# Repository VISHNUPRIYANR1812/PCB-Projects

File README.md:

# PCB-Projects
Collection of my custom PCB designs, including schematics, Gerber files, and project details.

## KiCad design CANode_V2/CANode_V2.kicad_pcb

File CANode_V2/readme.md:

#  SPI-CAN Node V1 to CANode V2: A SMARTER, WIRELESS UPGRADE! 

The V2 design introduces critical improvements to support wireless diagnostics, cloud integration, and real-time monitoring, making it a game-changer for CAN-based applications in automotive, industrial automation, and IoT systems.

## 🔍 V1 Limitations:

- MCP2515 CAN Controller with TJA1050 Transceiver provided standard SPI-CAN conversion but lacked debugging capabilities.
- Requires host MCU for programming and Application circuit

  🔗 View SPI-CAN Node V1 here: https://github.com/VISHNUPRIYANR1812/PCB-Projects/tree/main/Isolated-SPI-CAN-Node

## ⚙️ V2 Enhancements & Architecture:

https://github.com/user-attachments/assets/42ad2c8d-1fca-4bb1-90af-36ff37ddd96d

### ✅ MCU Upgrade:
- ESP8266 with Wi-Fi connectivity for remote CAN node management, cloud logging, and OTA updates.

### ✅ Level Shifting:
- TXB0108PWR Bi-Directional Logic Converter for seamless 3.3V↔5V communication between ESP8266 and MCP2515.

### ✅ CAN Controller & Transceiver:
- MCP2515 SPI-CAN Controller paired with TJA1050 CAN Transceiver for robust CAN communication.

### ✅ USB-UART Debugging:
- CH340G UART Controller with RTS/DTR auto-reset for hassle-free firmware updates and debugging.

### ✅ Power Management:
- LD1117S12TR LDO Regulator ensuring a stable 3.3V supply for ESP8266 and MCP2515.

### ✅ Termination & Protection:
- JST_XH 5V Power Connector for secure power input.
- 120Ω selectable CAN termination for network flexibility.
- ESD protection components for enhanced durability.

### ✅ Display & Expansion:
- OLED Display Header for real-time CAN message visualization.

## 💡 Key Advancements:
- 🚀 **IoT-enabled CAN Network** – Cloud integration, remote diagnostics, and OTA firmware updates.
- 🚀 **Wi-Fi-based Configuration** – Web dashboard for real-time monitoring & control.
- 🚀 **Advanced Debugging & Expansion** – Improved power stability, logic isolation, and interface flexibility.

This V2 iteration brings higher integration, improved debugging, and wireless intelligence, redefining modern embedded networking for automotive, industrial, and IoT applications.

## 📌 Hashtags:
#CANBus #IoT #EmbeddedSystems #ESP8266 #MCP2515 #PCBDesign #WirelessCommunication #EdgeComputing #IndustrialAutomation #CloudIntegration #Automation #SmartDevices #IoTDevelopment #SmartManufacturing #OpenSourceHardware #HardwareDesign #CircuitDesign #IoTNetworking #IoTSolutions #ProductDevelopment #TechInnovation

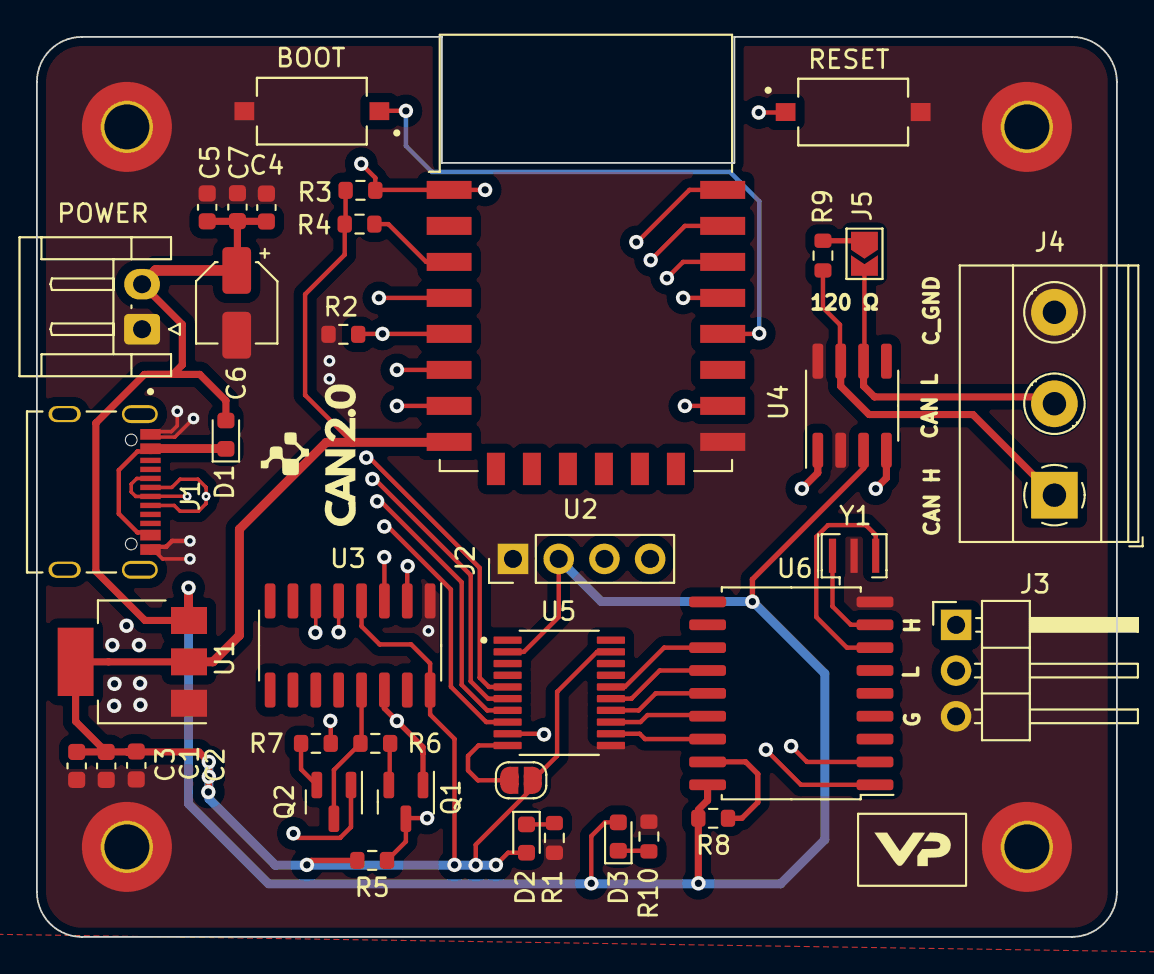
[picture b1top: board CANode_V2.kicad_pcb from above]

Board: 4 copper layers, 60.0 x 50.0 mm, 42 parts (0 on the bottom side), 38 nets.

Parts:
BOOT: BOOT0; SW_TS09-63-25-WT-260-SMT-TR
C1: 22uF; C_0603_1608Metric
C2: 10uF; C_0603_1608Metric
C3, C5, C7: 0.1uF; C_0603_1608Metric
C4: 100nF; C_0603_1608Metric
C6: 10uFE/16V; CP_Elec_4x3
D1: SS34; D_0603_1608Metric
D2, D3: LED; LED_0603_1608Metric
H1, H2, H3, H4: MountingHole_Pad; MountingHole_2.5mm_Pad_TopBottom
J1: USB_C; VALCON_CSP-USC16-TR
J2: I2C; PinHeader_1x04_P2.54mm_Vertical
J3: JUMP_CAN; PinHeader_1x03_P2.54mm_Horizontal
J4: SCR_CAN; TerminalBlock_Phoenix_MKDS-1,5-3-5.08_1x03_P5.08mm_Horizont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
J5: 120R_T; SolderJumper-2_P1.3mm_Open_TrianglePad1.0x1.5mm
JP1: OE; SolderJumper-2_P1.3mm_Open_RoundedPad1.0x1.5mm
POWER: PW_IN; JST_EH_S2B-EH_1x02_P2.50mm_Horizontal
Q1, Q2: S8050; SOT-23
R1, R2, R3, R4, R5, R6, R7, R8, R10: 10K; R_0603_1608Metric
R9: 120R; R_0603_1608Metric
RESET: NRST; SW_TS09-63-25-WT-260-SMT-TR
U1: LD1117S12TR_SOT223; SOT-223-3_TabPin2
U2: ESP-12F; ESP-12E
U3: CH340C; SOIC-16_3.9x9.9mm_P1.27mm
U4: TJA1050; SOIC-8_3.9x4.9mm_P1.27mm
U5: TXB0108PWR; SOP65P640X120-20N
U6: MCP2515-xSO; SOIC-18W_7.5x11.6mm_P1.27mm
Y1: 8MHz/22pF; Resonator_SMD_Murata_CSTxExxV-3Pin_3.0x1.1mm

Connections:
+3V3: C1.2, C2.2, C3.2, D2.2 (A), JP1.2 (B), R3.2, R4.2, R5.2, U1.2 (VO), U2.8 (VCC), U3.4 (V3), U3.16 (VCC), U5.19 (VCCB)
CAN_H: J3.1, J4.1, R9.1, U4.7 (CAN_H)
CAN_L: J3.2, J4.2, J5.2, U4.6 (CAN_L)
CRX: U4.4 (RXD), U6.2 (RXCAN)
CS: U5.12 (B8), U6.16 (~CS)
CTX: U4.1 (TXD), U6.1 (TXCAN)
D+: J1.A6 (D+), J1.B6 (D+), U3.5 (UD+)
D-: J1.A7 (D-), J1.B7 (D-), U3.6 (UD-)
DTR: Q1.1 (E), R7.1, U3.14 (~RTS)
EN: R4.1, U2.3 (EN)
GND: BOOT.2, C1.1, C2.1, C3.1, C4.1, C5.2, C6.2, C7.2, H1.1, H2.1, H3.1, H4.1, J1.A1 (GND), J1.A12 (GND), J1.B1 (GND), J1.B12 (GND), J2.1, J3.3, J4.3, POWER.1, R1.1, R2.1, R10.1, RESET.2, U1.1 (GND), U2.15 (GND), U3.1 (GND), U4.2 (GND), U4.8 (S), U5.11 (GND), U6.9 (VSS), Y1.2
GPIO0: BOOT.1, Q1.3 (C), R5.1, U2.18 (GPIO0)
GPIO1: U2.22 (GPIO1/TXD), U3.3 (RXD)
GPIO3: U2.21 (GPIO3/RXD), U3.2 (TXD)
GPIO4: J2.4, U2.19 (GPIO4)
GPIO5: J2.3, U2.20 (GPIO5)
GPIO12: U2.6 (GPIO12), U5.8 (A7)
GPIO13: U2.7 (GPIO13), U5.7 (A6)
GPIO14: R2.2, U2.5 (GPIO14), U5.6 (A5)
GPIO15: U2.16 (GPIO15), U5.9 (A8)
GPIO16: U2.4 (GPIO16), U5.5 (A4)
INT: U5.16 (B4), U6.12 (~INT)
MISO: U5.13 (B7), U6.15 (SO)
MOSI: U5.14 (B6), U6.14 (SI)
unnamed: D2.1 (K), R1.2
unnamed: D3.1 (K), R10.2
unnamed: D1.1 (K), J1.A4 (VBUS), J1.A9 (VBUS), J1.B4 (VBUS), J1.B9 (VBUS)
unnamed: J5.1, R9.2
unnamed: JP1.1 (A), U5.10 (OE)
unnamed: Q1.2 (B), R6.2
unnamed: Q2.2 (B), R7.2
unnamed: R8.2, U6.17 (~RESET)
unnamed: U6.7 (OSC2), Y1.3
unnamed: U6.8 (OSC1), Y1.1
RST: Q2.1 (E), R3.1, RESET.1, U2.1 (~RST)
RTS: Q2.3 (C), R6.1, U3.13 (~DTR)
SCK: U5.15 (B5), U6.13 (SCK)
VBUS: C4.2, C5.1, C6.1, C7.1, D1.2 (A), D3.2 (A), J2.2, POWER.2, R8.1, U1.3 (VI), U4.3 (VCC), U5.2 (VCCA), U6.18 (VDD)

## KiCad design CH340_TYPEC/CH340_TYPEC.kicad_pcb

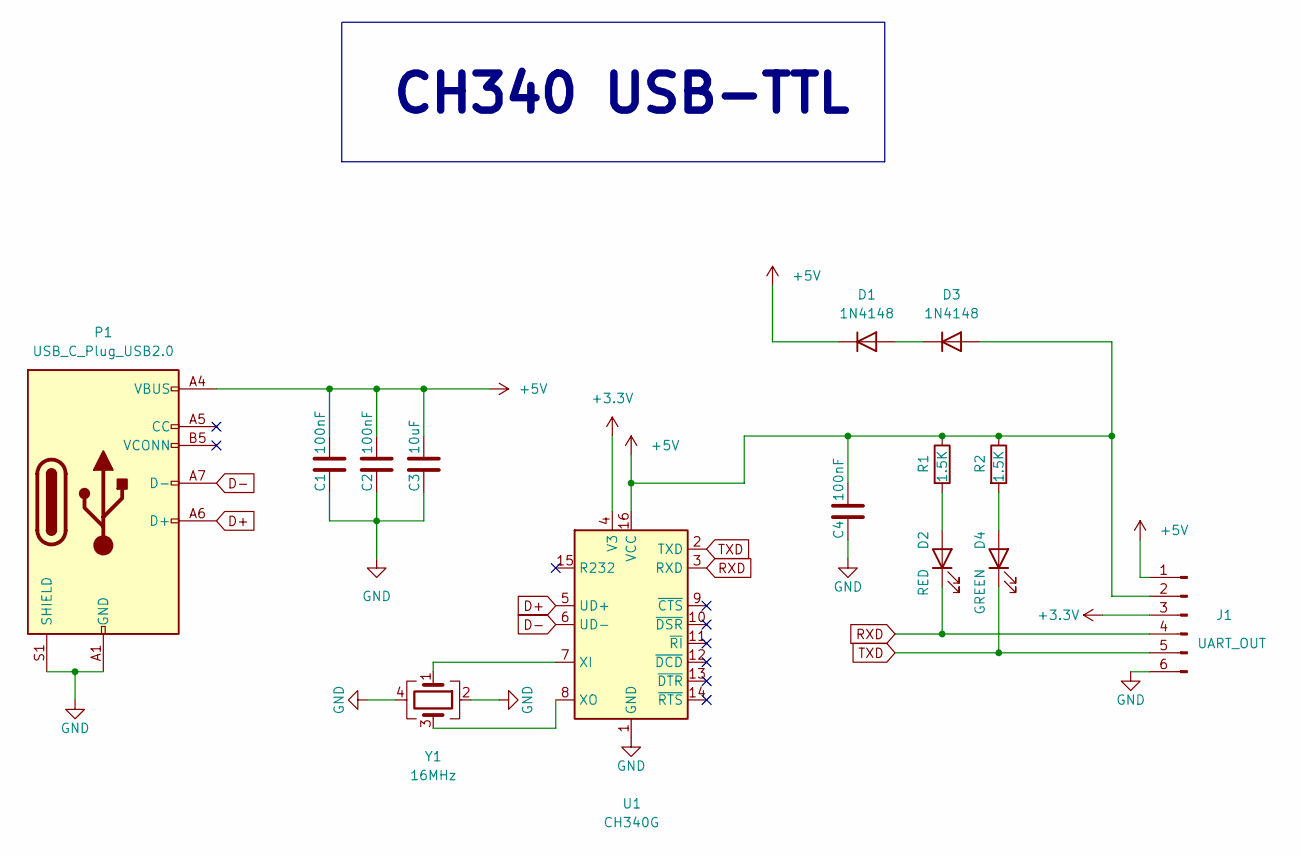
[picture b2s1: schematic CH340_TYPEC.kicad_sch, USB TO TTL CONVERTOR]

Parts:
C1, C2, C4: 100nF; C_0603_1608Metric
C3: 10uF; C_0603_1608Metric
D1, D3: 1N4148; D_SOD-123F
D2: RED; LED_0603_1608Metric
D4: GREEN; LED_0603_1608Metric
J1: UART_OUT; PinHeader_1x06_P2.54mm_Horizontal
P1: USB_C_Plug_USB2.0; USB_C_Receptacle_HRO_TYPE-C-31-M-12
R1, R2: 1.5K; R_0603_1608Metric
U1: CH340G; SOIC-16_3.9x9.9mm_P1.27mm
Y1: 16MHz; Crystal_SMD_3225-4Pin_3.2x2.5mm

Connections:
+3V3: J1.3, U1.4 (V3)
+5V: C1.1, C2.1, C3.1, C4.1, D1.1 (K), D3.2 (A), J1.1, J1.2, P1.A4 (VBUS), P1.A9 (VBUS), P1.B4 (VBUS), P1.B9 (VBUS), R1.1, R2.1, U1.16 (VCC)
D+: P1.A6 (D+), U1.5 (UD+)
D-: P1.A7 (D-), U1.6 (UD-)
GND: C1.2, C2.2, C3.2, C4.2, J1.6, P1.A1 (GND), P1.A12 (GND), P1.B1 (GND), P1.B12 (GND), P1.S1 (SHIELD), U1.1 (GND), Y1.2, Y1.4
unnamed: D1.2 (A), D3.1 (K)
unnamed: D2.2 (A), R1.2
unnamed: D4.2 (A), R2.2
unnamed: U1.7 (XI), Y1.1
unnamed: U1.8 (XO), Y1.3
RXD: D2.1 (K), J1.4, U1.3 (RXD)
TXD: D4.1 (K), J1.5, U1.2 (TXD)

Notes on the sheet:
CH340 USB-TTL

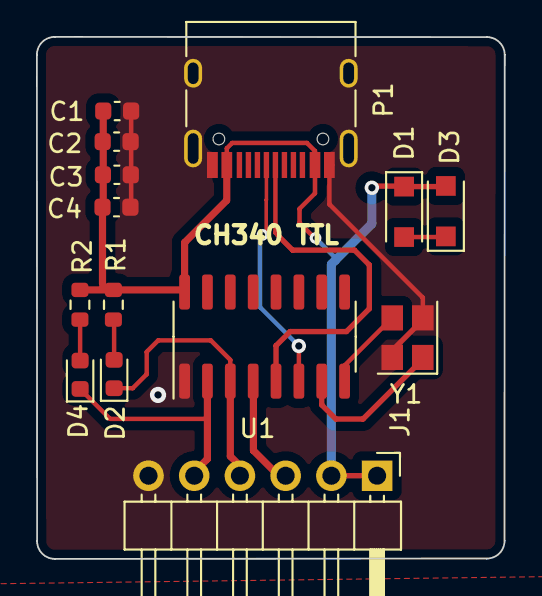
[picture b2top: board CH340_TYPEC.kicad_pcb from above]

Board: 2 copper layers, 26.0 x 29.0 mm, 14 parts (0 on the bottom side), 12 nets.

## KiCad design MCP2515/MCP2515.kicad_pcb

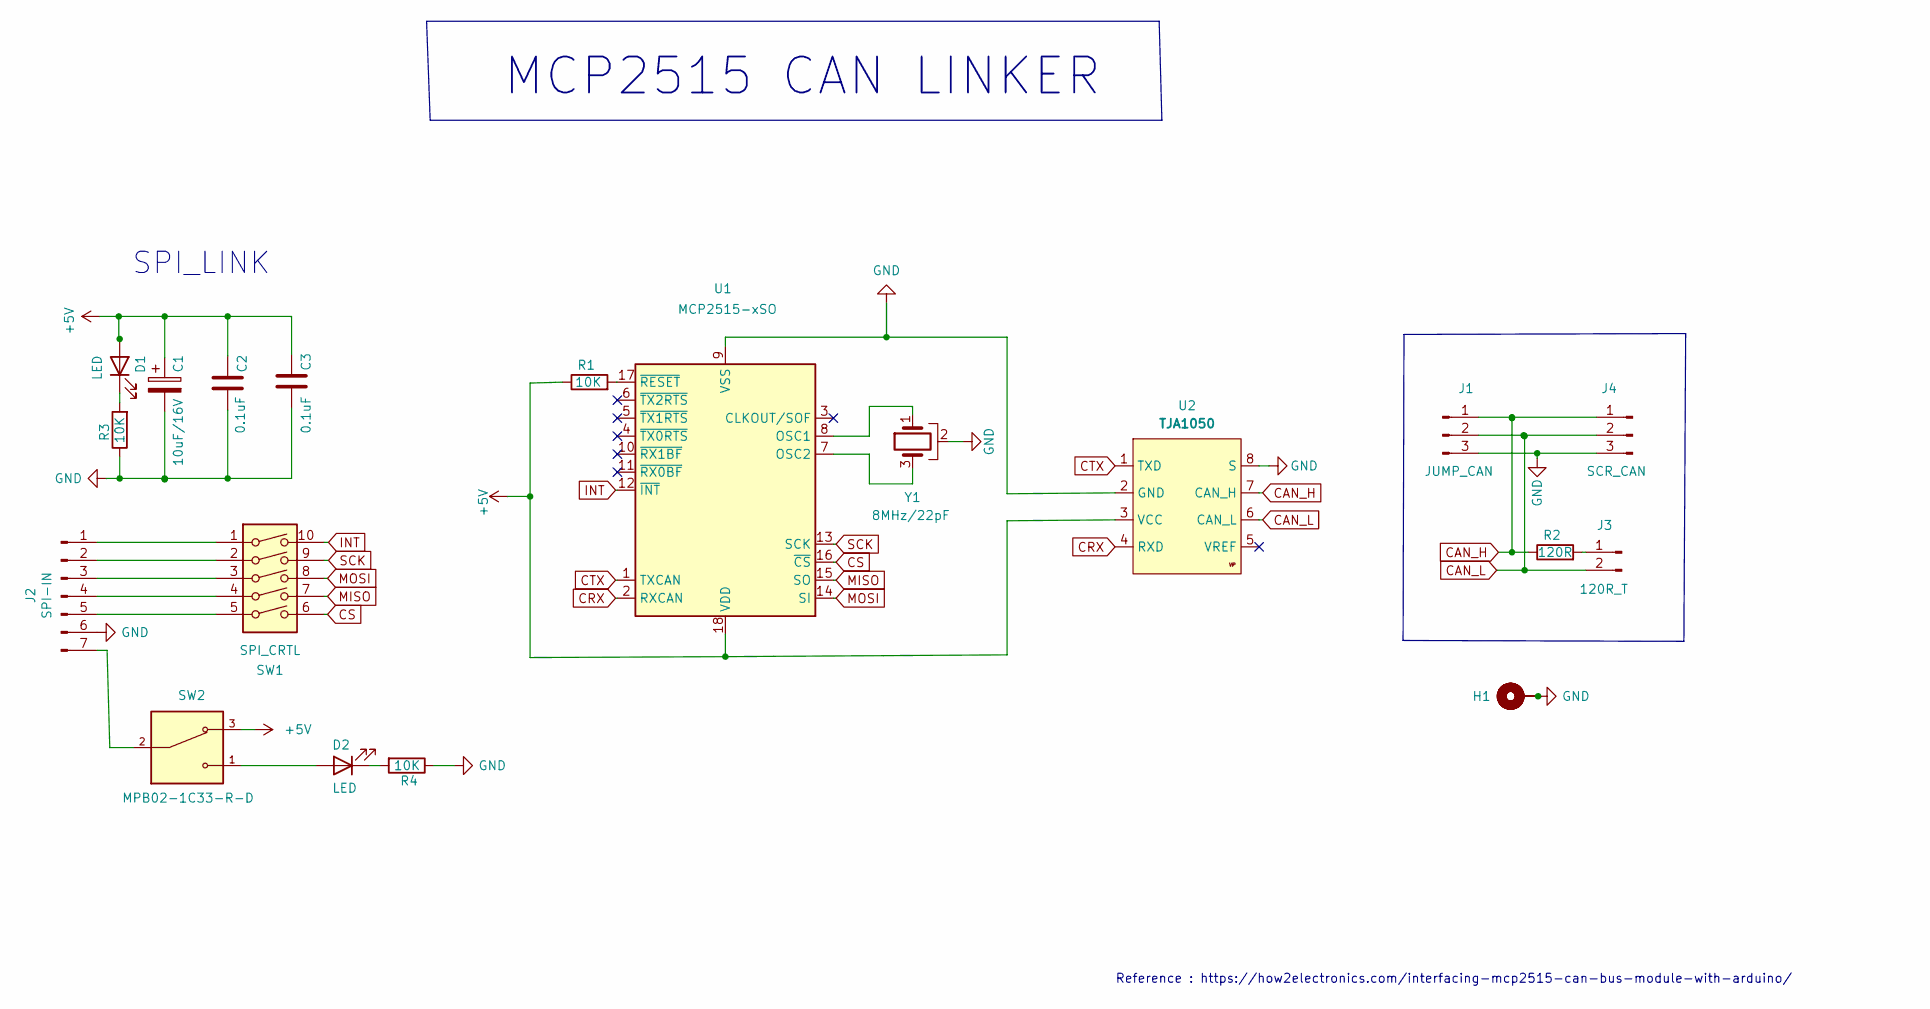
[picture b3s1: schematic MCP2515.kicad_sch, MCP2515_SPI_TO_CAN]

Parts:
C1: 10uF/16V; CP_Elec_4x3
C2, C3: 0.1uF; C_0805_2012Metric
D1, D2: LED; LED_0805_2012Metric
H1, H2, H3, H4: MountingHole_Pad; MountingHole_2.5mm_Pad_TopBottom
J1: JUMP_CAN; PinHeader_1x03_P2.54mm_Horizontal
J2: SPI-IN; PinHeader_1x07_P2.54mm_Vertical
J3: 120R_T; SolderJumper-2_P1.3mm_Open_TrianglePad1.0x1.5mm
J4: SCR_CAN; TerminalBlock_Phoenix_MKDS-1,5-3-5.08_1x03_P5.08mm_Horizont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
R1, R3, R4: 10K; R_0805_2012Metric
R2: 120R; R_0805_2012Metric
SW1: SPI_CRTL; SW_DIP_SPSTx05_Slide_KingTek_DSHP05TS_W7.62mm_P1.27mm
SW2: MPB02-1C33-R-D; SW_MPB02-1C33-R-D; PARTREV 1.0
U1: MCP2515-xSO; SOIC-18W_7.5x11.6mm_P1.27mm; LCSC C153782
U2: TJA1050; SOIC-8_3.9x4.9mm_P1.27mm; LCSC C6952
Y1: 8MHz/22pF; Resonator_SMD_Murata_CSTxExxV-3Pin_3.0x1.1mm

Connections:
+5V: C1.1, C2.1, C3.1, D1.2 (A), R1.1, SW2.3, U1.18 (VDD), U2.3 (VCC)
CAN_H: J1.1, J4.1, R2.1, U2.7 (CAN_H)
CAN_L: J1.2, J3.2, J4.2, U2.6 (CAN_L)
CRX: U1.2 (RXCAN), U2.4 (RXD)
CS: SW1.6, U1.16 (~CS)
CTX: U1.1 (TXCAN), U2.1 (TXD)
INT: SW1.10, U1.12 (~INT)
MISO: SW1.7, U1.15 (SO)
MOSI: SW1.8, U1.14 (SI)
unnamed: D1.1 (K), R3.2
unnamed: D2.1 (K), R4.2
unnamed: D2.2 (A), SW2.1
unnamed: J2.1, SW1.1
unnamed: J2.2, SW1.2
unnamed: J2.3, SW1.3
unnamed: J2.4, SW1.4
unnamed: J2.5, SW1.5
unnamed: J2.7, SW2.2
unnamed: J3.1, R2.2
unnamed: R1.2, U1.17 (~RESET)
unnamed: U1.7 (OSC2), Y1.3
unnamed: U1.8 (OSC1), Y1.1
SCK: SW1.9, U1.13 (SCK)

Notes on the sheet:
Reference : https://how2electronics.com/interfacing-mcp2515-can-bus-module-with-arduino/
MCP2515 CAN LINKER
SPI_LINK

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
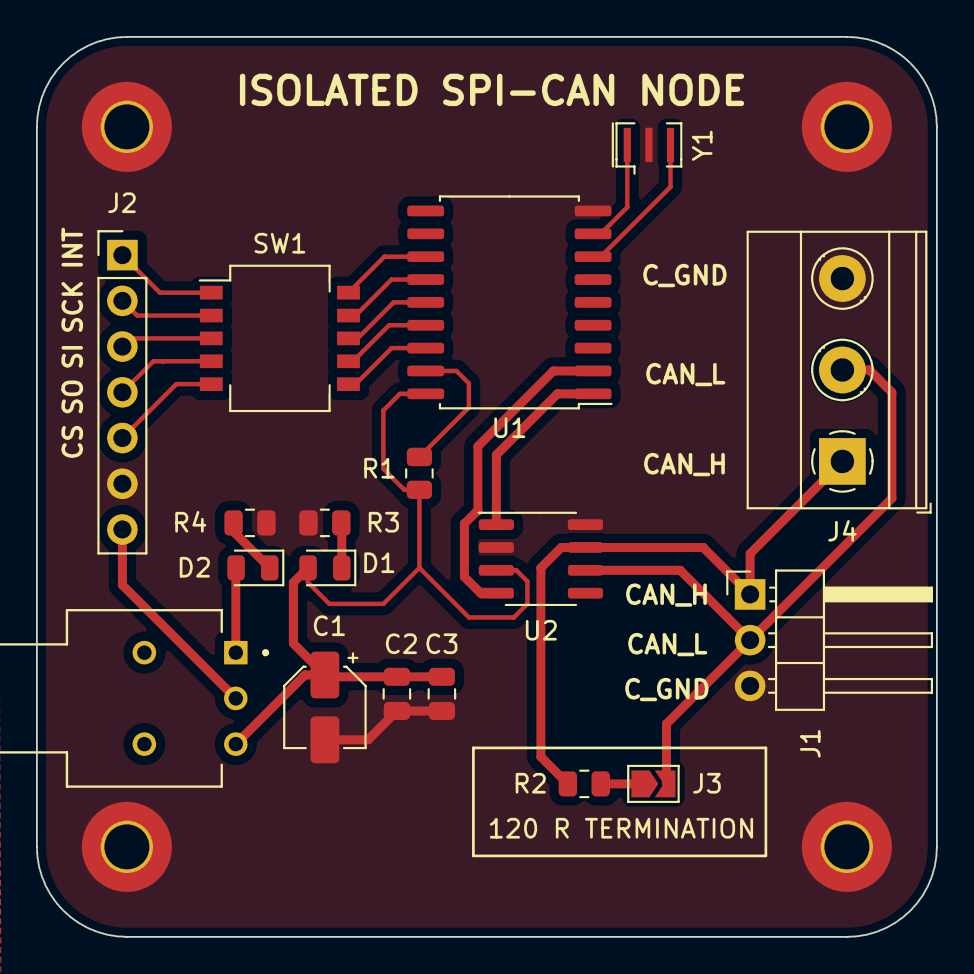
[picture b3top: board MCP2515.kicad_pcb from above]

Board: 2 copper layers, 50.0 x 50.0 mm, 22 parts (0 on the bottom side), 24 nets.

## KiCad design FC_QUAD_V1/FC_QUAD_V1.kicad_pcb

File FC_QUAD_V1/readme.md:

Here my latest custom-designed flight controller PCB, developed for Cost effective & Minimalistic solid performance drone applications. This design integrates essential features for real-time flight control, precise navigation, and efficient data handling, making it a robust solution for UAV systems.

## 🔹 System Specifications:

- **MCU:** STM32F411CEU6 – ARM Cortex-M4 FPU for real-time processing.
- **10 DOF IMU for precise motion sensing:**
  - **TDK MPU6050** – 6-axis gyroscope & accelerometer for stabilization.
  - **Honeywell HMC5883L** – 3-axis mag for accurate heading estimation.
  - **Bosch BMP180** – H-precision barometric sensor for altitude data.
- **SBUS input** for receiver communication.
- **UART interface** for GPS module integration.
- **SPI Testpoint** for Blackbox logging & mission data storage.
- **I2C support** up to 800KHz with an external I2C port for sensor expansion.
- **USB-C interface** for firmware updates, tuning, and debugging.
- **RGB Neo-pixel LED** support for status indication.
- **JST_XH connector** for power module with V_SENSE & I_SENSE for real-time voltage & current monitoring.

## 🔹 PCB Specifications:

- **4-layer PCB stack-up** optimized for signal integrity & thermal performance:
  - **Layer 1:** Mixed plane (high-speed signals & power distribution).
  - **Layer 2:** Signal plane (optimized routing for minimal EMI).
  - **Layer 3:** Dedicated ground plane (low-noise operation).
  - **Layer 4:** Power plane (stable power distribution).
- **Thermal relief vias** to enhance heat dissipation.
- **Copper-filled unused regions** for improved EMC and signal integrity.
- **Well-organized ports and pin configurations** for seamless connectivity.

This project was designed with a focus on cost-efficiency, modularity, and real-time performance to meet the demands of modern UAV systems. Looking forward to further testing and optimizations.

Would love to hear your thoughts and feedback!

### Hashtags:

#PCBDesign #EmbeddedSystems #UAVTechnology #ElectronicsEngineering #AutonomousSystems #FutureOfDrones  
#DroneIndia #TechTrends #AviationMastery #DroneCareers

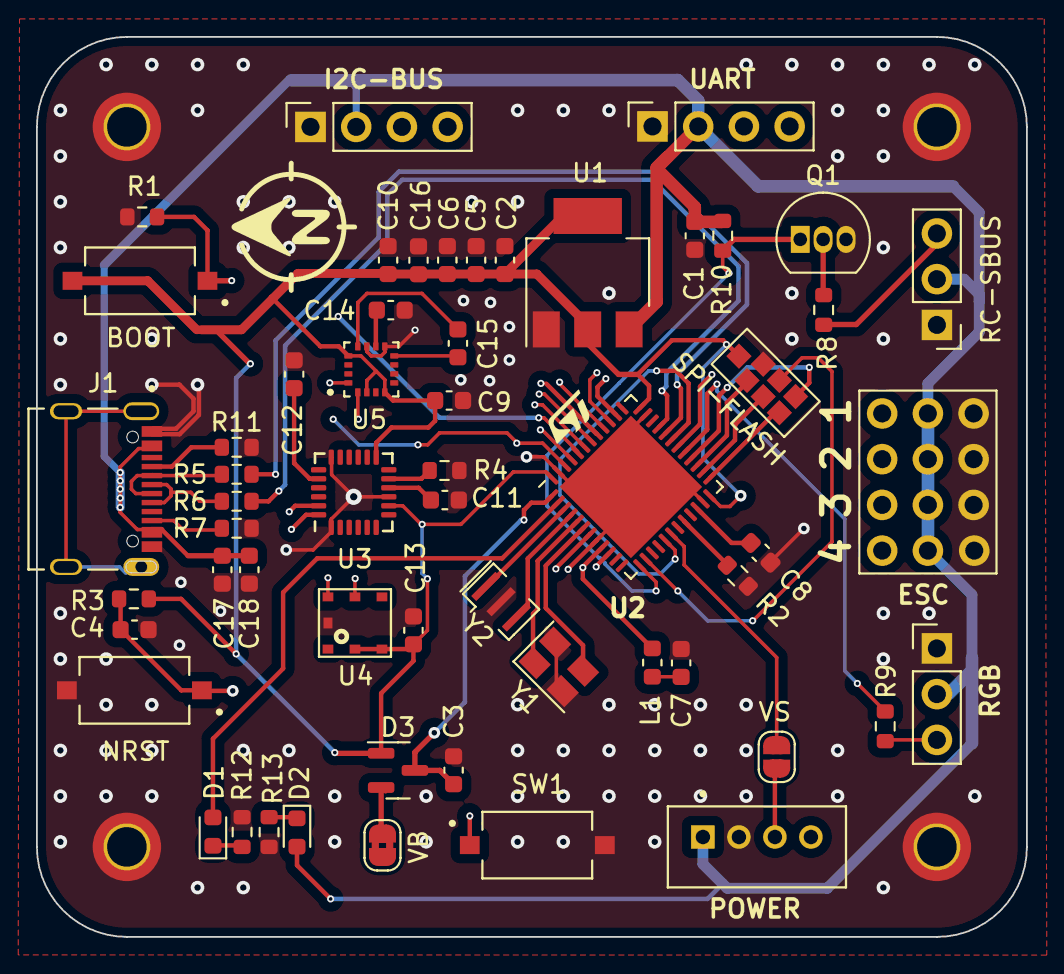
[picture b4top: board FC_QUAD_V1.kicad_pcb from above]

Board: 4 copper layers, 55.0 x 50.0 mm, 60 parts (0 on the bottom side), 53 nets.

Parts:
BOOT: BOOT0; SW_TS09-63-25-WT-260-SMT-TR
C1, C2, C4, C5, C6, C7, C17, C18: 100nF; C_0603_1608Metric
C3: 100uF; C_0603_1608Metric
C8: 2.2uF; C_0603_1608Metric
C9: 0.01uF; C_0603_1608Metric
C10, C11, C13, C16: 0.1uF; C_0603_1608Metric
C12: 2.2nF; C_0603_1608Metric
C14: 4.7uF; C_0603_1608Metric
C15: 0.22uF; C_0603_1608Metric
D1, D2: LED; LED_0603_1608Metric
D3: BAT54C; SOT-23
ESC: 4PIN_ESC; Esc_connector_4M
H1, H2, H3, H4: MountingHole_Pad; MountingHole_2.2mm_M2_DIN965_Pad_TopBottom
I2C-BUS: I2C; PinSocket_1x04_P2.54mm_Vertical
J1: CSP-USC16-TR; VALCON_CSP-USC16-TR
L1: 10uH; L_0603_1608Metric
NRST: NRST; SW_TS09-63-25-WT-260-SMT-TR
POWER: POWER MODULE; JST_B4B-PH-K
Q1: BC547; TO-92_Inline
R1, R2, R10, R12, R13: 10K; R_0603_1608Metric
R3: NC; R_0603_1608Metric
R4: 1K; R_0603_1608Metric
R5, R6: 10R; R_0603_1608Metric
R7, R11: 5.8K; R_0603_1608Metric
R8: 4.7K; R_0603_1608Metric
R9: 470R; R_0603_1608Metric
RC-SBUS: SBUS; PinHeader_1x03_P2.54mm_Vertical
RGB: RGB; PinHeader_1x03_P2.54mm_Vertical
SPI-FLASH: SPI-BLACKBOX; 7_TP
SW1: KEY; SW_TS09-63-25-WT-260-SMT-TR
U1: LD1117S12TR_SOT223; SOT-223-3_TabPin2
U2: STM32F411CEUx; QFN-48-1EP_7x7mm_P0.5mm_EP5.6x5.6mm
U3: MPU-6050; InvenSense_QFN-24_4x4mm_P0.5mm
U4: BMP180
U5: HMC5883L-TR
UART: UART; PinSocket_1x04_P2.54mm_Vertical
VB: VBAT; SolderJumper-2_P1.3mm_Bridged2Bar_RoundedPad1.0x1.5mm
VS: V_SENSE; SolderJumper-2_P1.3mm_Open_RoundedPad1.0x1.5mm
Y1: 25MHz/12pF; Crystal_SMD_SeikoEpson_TSX3225-4Pin_3.2x2.5mm
Y2: 32.7KHz/6pF; Resonator_SMD_Murata_CSTxExxV-3Pin_3.0x1.1mm

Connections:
+3V3: BOOT.2, C2.2, C5.2, C6.2, C9.2, C10.2, C13.2, C16.1, D3.1, R3.1, SPI-FLASH.7, U1.2 (VO), U2.24 (VDD), U2.36 (VDD), U2.48 (VDD), U3.8 (VDDIO), U3.13 (VDD), U4.2 (VDD), U4.3 (VDDIO), U5.2 (VDD), U5.4 (S1), U5.13 (VDDIO)
BOOT0: BOOT.1, R1.2, U2.44 (BOOT0)
CS: SPI-FLASH.5, U2.14 (PA4)
DN: J1.A7 (DN1), J1.B7 (DN2), R5.1
DP: J1.A6 (DP1), J1.B6 (DP2), R6.1
GND: C1.1, C2.1, C3.2, C4.2, C5.1, C6.1, C7.1, C8.1, C9.1, C10.1, C11.1, C12.2, C13.1, C14.1, C16.2, C17.1, C18.1, ESC.1 (GND), ESC.2 (GND), ESC.3 (GND), ESC.4 (GND), H1.1, H2.1, H3.1, H4.1, I2C-BUS.1, J1.A1 (GND_A), J1.A12 (GND_A), J1.B1 (GND_B), J1.B12 (GND_B), NRST.2, POWER.2, Q1.3 (E), R1.1, R2.1, R4.1, R7.2, R11.1, R12.2, R13.2, RC-SBUS.1, RGB.1, SPI-FLASH.6, SW1.2, U1.1 (GND), U2.8 (VSSA), U2.23 (VSS), U2.35 (VSS), U2.47 (VSS), U2.49 (VSS), U3.1 (CLKIN), U3.9 (AD0), U3.18 (GND), U4.7 (GND), U5.9 (GND), U5.11 (GND), UART.1, Y1.2, Y1.4, Y2.2
MISO: SPI-FLASH.3, U2.27 (PB14)
MOSI: SPI-FLASH.4, U2.28 (PB15)
MOT1: ESC.9 (M1), U2.40 (PB4)
MOT2: ESC.10 (M2), U2.41 (PB5)
MOT3: ESC.11 (M3), U2.42 (PB6)
MOT4: ESC.12 (M4), U2.43 (PB7)
NRST: C4.1, NRST.1, R3.2, U2.7 (NRST)
NSS: SPI-FLASH.1, U2.25 (PB12)
unnamed: C8.2, U2.22 (VCAP1)
unnamed: C11.2, U3.10 (REGOUT)
unnamed: C12.1, U3.20 (CPOUT)
unnamed: C14.2, U5.10 (C1)
unnamed: C15.1, U5.12 (SETC)
unnamed: C15.2, U5.8 (SETP)
unnamed: D1.1 (K), R12.1
unnamed: D2.1 (K), R13.1
unnamed: D3.2, VB.1 (A)
unnamed: J1.A5 (CC1), R11.2
unnamed: J1.B5 (CC2), R7.1
unnamed: R9.1, RGB.3
unnamed: R8.2, RC-SBUS.3
unnamed: L1.1, U2.9 (VDDA)
unnamed: Q1.2 (B), R8.1
unnamed: R4.2, U3.11 (FSYNC)
PA0: SW1.1, U2.10 (PA0)
PA3: Q1.1 (C), R10.2, U2.13 (PA3)
PA8: R9.2, U2.29 (PA8)
PA10: U2.17 (PA7), U2.31 (PA10)
PA11: R5.2, U2.32 (PA11)
PA12: R6.2, U2.33 (PA12)
PB0: U2.18 (PB0), VS.1 (A)
PB2: R2.2, U2.20 (PB2)
PB8: I2C-BUS.4, U2.45 (PB8), U3.23 (SCL), U4.5 (SCL), U5.1 (SCL)
PB9: I2C-BUS.3, U2.46 (PB9), U3.24 (SDA), U4.6 (SDA), U5.16 (SDA)
PB13: SPI-FLASH.2, U2.26 (PB13)
PC13: D1.2 (A), U2.2 (PC13)
PC14: U2.3 (PC14), Y2.1
PC15: U2.4 (PC15), Y2.3
PH0: U2.5 (PH0), Y1.1
PH1: U2.6 (PH1), Y1.3
RX: U2.38 (PA15), UART.4
SHELL_GND: J1.S1 (SHELL_GND), J1.S2 (SHELL_GND), J1.S3 (SHELL_GND), J1.S4 (SHELL_GND)
TX: U2.39 (PB3), UART.3
VBAT: C3.1, D3.3, U2.1 (VBAT)
VBUS: C1.2, C17.2, C18.2, D2.2 (A), ESC.5 (VCC), ESC.6 (VCC), ESC.7 (VCC), ESC.8 (VCC), I2C-BUS.2, J1.A4 (VBUS_A), J1.A9 (VBUS_A), J1.B4 (VBUS_B), J1.B9 (VBUS_B), POWER.1, R10.1, RC-SBUS.2, RGB.2, U1.3 (VI), UART.2
VDDA: C7.2, L1.2
V_SENSE: POWER.3, VS.2 (B)

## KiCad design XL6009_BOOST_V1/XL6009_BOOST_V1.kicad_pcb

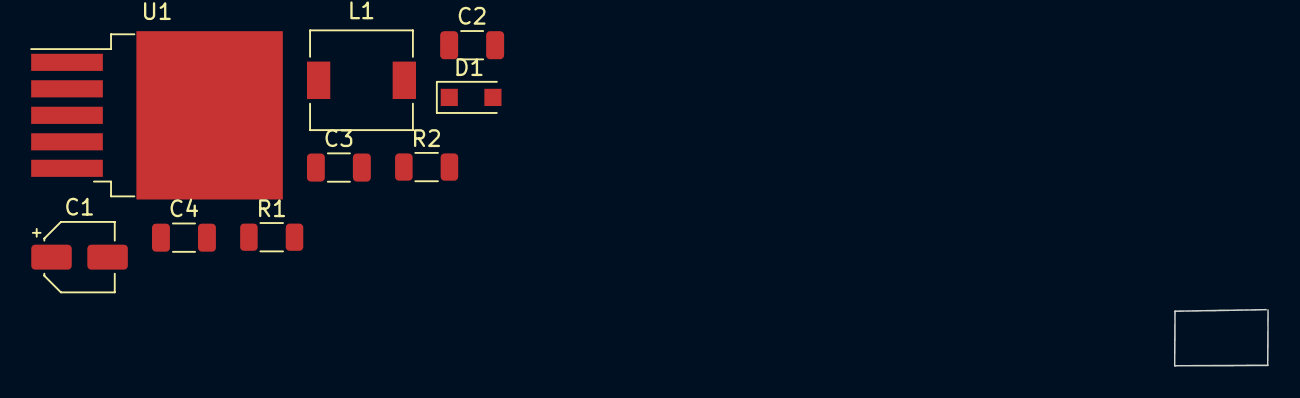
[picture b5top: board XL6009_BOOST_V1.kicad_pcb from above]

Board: 2 copper layers, 9 parts (0 on the bottom side), 6 nets, no tracks yet.

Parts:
C1: 47uF/60V; CP_Elec_4x5.3
C2, C3: 1uF; C_1206_3216Metric
C4: 220uF/50V; C_1206_3216Metric
D1: SS34; D_SOD-123F
L1: 47uH; L_6.3x6.3_H3
R1: 60K; R_1206_3216Metric
R2: 1K; R_1206_3216Metric
U1: XL6009; TO-263-5_TabPin6

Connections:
IN+: C1.1, C2.1, L1.1, U1.4 (VIN)
IN-: C1.2, C2.2, U1.1 (GND)
unnamed: D1.1 (A), L1.2, U1.3 (SW)
unnamed: R1.2, R2.1, U1.5 (FB)
VOUT+: C3.1, C4.1, D1.2 (K), R1.1
VOUT-: C3.2, C4.2, R2.2

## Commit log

2025-01-28 Create Isolated_SPI-CAN_Node
2025-01-28 Rename MCP2515.kicad_prl to Isolated-SPI-CAN-Node/MCP2515.kicad_prl
2025-01-28 Schematic
2025-01-28 KiCAD 6 Project file
2025-01-28 README.md
2025-01-28 Total_files
2025-02-01 Added ch340 files
2025-02-01 XL6009
2025-02-01 Create fp-info-cache
2025-02-01 Remove
2025-02-05 Main_files_FMU
2025-02-06 CAN_module
2025-02-06 remove all
2025-02-06 Main_update
2025-02-16 CANode_V2
